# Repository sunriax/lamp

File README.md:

# Controllable Lamp (Signal) over Wireless LAN ([Shelly](https://shop.shelly.cloud/shelly-1-wifi-smart-home-automation#50))

## Project description

The PCB (lamp) can be controlled over a [Shelly](https://shop.shelly.cloud/shelly-1-wifi-smart-home-automation#50) wireless LAN module. It is attached to the PCB and can be controlled over the [Web Control](http://sunriax.github.io/lamp/) interface or any other software. Currently the lamp is designed for alerting. It changes the color within a given time. The lamp can be configured over the [Lamp Control](https://github.com/sunriax/lamp/releases/download/v1.0/Lamp.zip) application. Also the attached PC can be informed that an alert (over wireless LAN) occurrs. The current firmware can be downloaded [here](https://github.com/sunriax/lamp/releases/download/v1.0-Firmware/Firmware.zip). An ISP programmer for ATmega8 is necessary to flash the firmware onto the PCB.

## Project status

### Application

| Program     | Status |
|-------------|--------|
| [Web Control](http://sunriax.github.io/lamp/) |  |
| [Application](https://github.com/sunriax/lamp/releases/download/v1.0/Lamp.zip) |  |
|             |  |
| [Firmware](https://github.com/sunriax/lamp/releases/download/v1.0-Firmware/Firmware.zip)    |  |

### Schematic/PCB

| Board | Status |
|-------|:------:|
| [Schematic](https://cadlab.io/project/23814/main/circuit/cGNiL3BjYi5zY2g%3D) | ✔️ Done |
| [Board](https://cadlab.io/project/23814/main/circuit/cGNiL3BjYi5raWNhZF9wY2I%3D) | ✔️ Done |
| [Partlist](partlist.csv) | ✔️ Done |
| Production | ✔️ Done |
| [Assembly](pcb_assembled.png) | ✔️ Done |
| Case | ❌ Open |

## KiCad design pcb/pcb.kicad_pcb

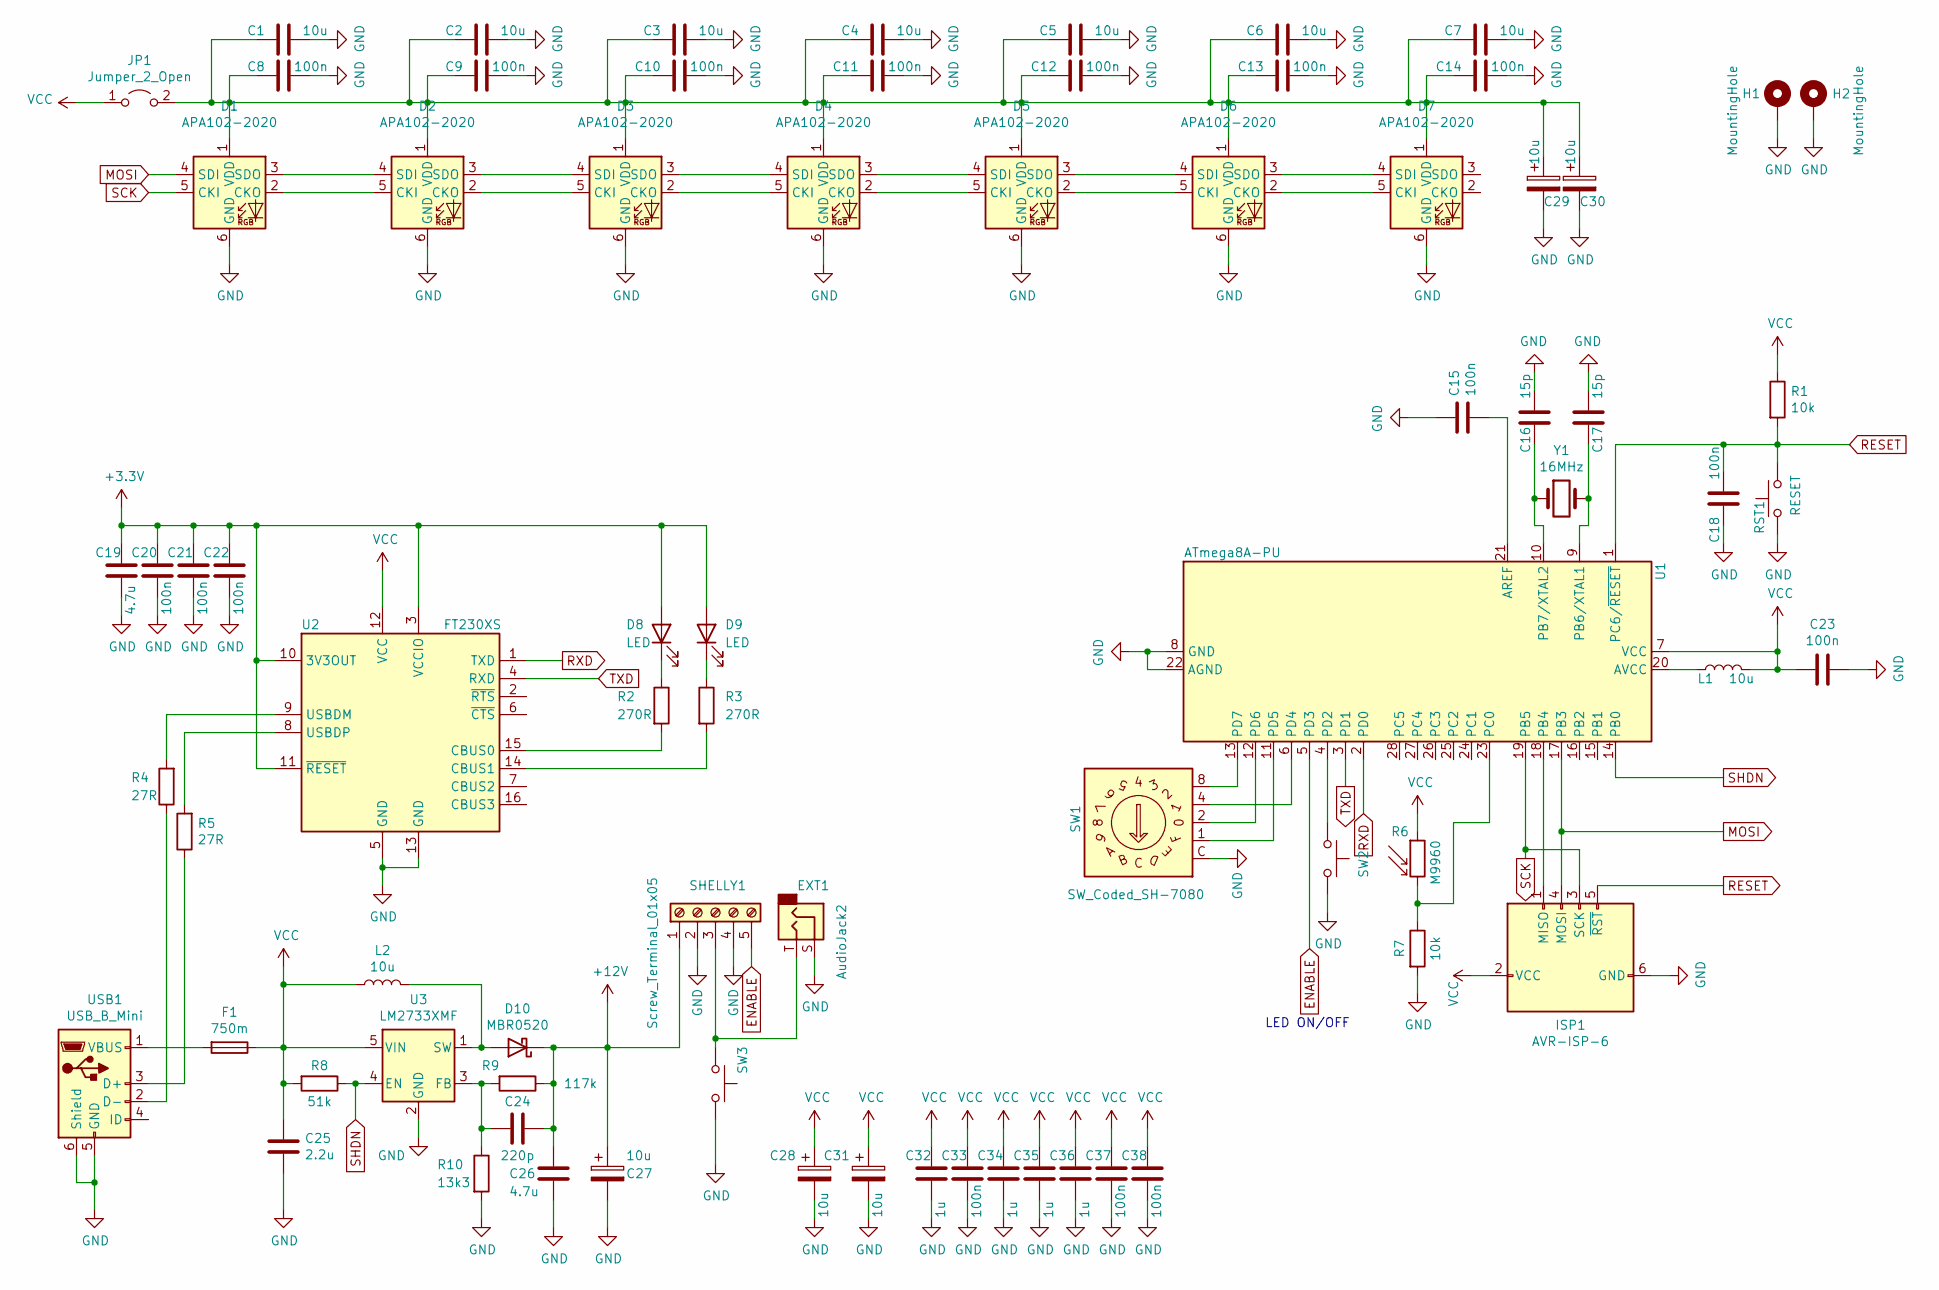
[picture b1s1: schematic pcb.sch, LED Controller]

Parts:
C1, C2, C3, C4, C5, C6, C7: 10u; C_0603_1608Metric
C8, C9, C10, C11, C12, C13, C14, C15, C18, C20, C21, C22, C23, C33, C37, C38: 100n; C_0603_1608Metric
C16, C17: 15p; C_0603_1608Metric
C19, C26: 4.7u; C_0603_1608Metric
C24: 220p; C_0603_1608Metric
C25: 2.2u; C_0603_1608Metric
C27, C28, C29, C30, C31: 10u; CP_Elec_4x5.8
C32, C34, C35, C36: 1u; C_0603_1608Metric
D1, D2, D3, D4, D5, D6, D7: APA102-2020; LED-APA102-2020
D8, D9: LED; LED_0603_1608Metric
D10: MBR0520; D_SOD-123
EXT1: AudioJack2; Jack_3.5mm_CUI_SJ-3523-SMT_Horizontal
F1: 750m; Fuse_Bourns_MF-SM_7.98x5.44mm
H1, H2: MountingHole; MountingHole_3.2mm_M3_Pad
ISP1: AVR-ISP-6; PinHeader_2x03_P2.54mm_Vertical_SMD
JP1: Jumper_2_Open; PinHeader_1x02_P2.54mm_Horizontal
L1: 10u; L_0805_2012Metric
L2: 10u; L_Bourns-SRN1060
R1, R7: 10k; R_0603_1608Metric
R2, R3: 270R; R_0603_1608Metric
R4, R5: 27R; R_0603_1608Metric
R6: M9960; R_LDR_5.2x5.2mm_P3.5mm_Horizontal
R8: 51k; R_0603_1608Metric
R9: 117k; R_0603_1608Metric
R10: 13k3; R_0603_1608Metric
RST1: RESET; SW_Push_1P1T-SH_NO_CK_KMR2xxG
SHELLY1: Screw_Terminal_01x05; TerminalBlock_Phoenix_MKDS-1,5-5_1x05_P5.00mm_Horizontal
SW1: SW_Coded_SH-7080; Nidec_Copal_SH-7040B
SW2, SW3: SW_Push_1P1T-SH_NO_CK_KMR2xxG
U1: ATmega8A-PU; DIP-28_W8.89mm_SMDSocket_LongPads
U2: FT230XS; SSOP-16_3.9x4.9mm_P0.635mm
U3: LM2733XMF; SOT-23-5
USB1: USB_B_Mini; USB_Mini-B_Lumberg_2486_01_Horizontal
Y1: 16MHz; Crystal_SMD_0603-2Pin_6.0x3.5mm

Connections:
+3V3: C19.2, C20.2, C21.2, C22.2, D8.2 (A), D9.2 (A), U2.3 (VCCIO), U2.10 (3V3OUT), U2.11 (~RESET)
+12V: C24.1, C26.1, C27.1, D10.1 (K), R9.1, SHELLY1.1
ENABLE: SHELLY1.5, U1.5 (PD3)
GND: C1.1, C2.1, C3.1, C4.1, C5.1, C6.1, C7.1, C8.1, C9.1, C10.1, C11.1, C12.1, C13.1, C14.1, C15.2, C16.2, C17.1, C18.2, C19.1, C20.1, C21.1, C22.1, C23.2, C25.2, C26.2, C27.2, C28.2, C29.2, C30.2, C31.2, C32.1, C33.1, C34.1, C35.1, C36.1, C37.1, C38.1, D1.6 (GND), D2.6 (GND), D3.6 (GND), D4.6 (GND), D5.6 (GND), D6.6 (GND), D7.6 (GND), EXT1.S, H1.1, H2.1, ISP1.6 (GND), R7.2, R10.2, RST1.1, SHELLY1.2, SHELLY1.4, SW1.C, SW2.1, SW3.1, U1.8 (GND), U1.22 (AGND), U2.5 (GND), U2.13 (GND), U3.2 (GND), USB1.5 (GND), USB1.6 (Shield)
MOSI: D1.4 (SDI), ISP1.4 (MOSI), U1.17 (PB3)
unnamed: C1.2, C2.2, C3.2, C4.2, C5.2, C6.2, C7.2, C8.2, C9.2, C10.2, C11.2, C12.2, C13.2, C14.2, C29.1, C30.1, D1.1 (VDD), D2.1 (VDD), D3.1 (VDD), D4.1 (VDD), D5.1 (VDD), D6.1 (VDD), D7.1 (VDD), JP1.2 (B)
unnamed: C15.1, U1.21 (AREF)
unnamed: C16.1, U1.10 (PB7/XTAL2), Y1.1
unnamed: C17.2, U1.9 (PB6/XTAL1), Y1.2
unnamed: C24.2, R9.2, R10.1, U3.3 (FB)
unnamed: D1.2 (CKO), D2.5 (CKI)
unnamed: D1.3 (SDO), D2.4 (SDI)
unnamed: D2.2 (CKO), D3.5 (CKI)
unnamed: D2.3 (SDO), D3.4 (SDI)
unnamed: D3.2 (CKO), D4.5 (CKI)
unnamed: D3.3 (SDO), D4.4 (SDI)
unnamed: D4.2 (CKO), D5.5 (CKI)
unnamed: D4.3 (SDO), D5.4 (SDI)
unnamed: D5.2 (CKO), D6.5 (CKI)
unnamed: D5.3 (SDO), D6.4 (SDI)
unnamed: D6.2 (CKO), D7.5 (CKI)
unnamed: D6.3 (SDO), D7.4 (SDI)
unnamed: D8.1 (K), R2.1
unnamed: D9.1 (K), R3.1
unnamed: D10.2 (A), L2.2, U3.1 (SW)
unnamed: EXT1.T, SHELLY1.3, SW3.2
unnamed: F1.2, USB1.1 (VBUS)
unnamed: ISP1.1 (MISO), U1.18 (PB4)
unnamed: L1.1, U1.20 (AVCC)
unnamed: R2.2, U2.15 (CBUS0)
unnamed: R3.2, U2.14 (CBUS1)
unnamed: R4.1, USB1.2 (D-)
unnamed: R4.2, U2.9 (USBDM)
unnamed: R5.1, USB1.3 (D+)
unnamed: R5.2, U2.8 (USBDP)
unnamed: R6.2, R7.1, U1.23 (PC0)
unnamed: SW1.1, U1.11 (PD5)
unnamed: SW1.2, U1.12 (PD6)
unnamed: SW1.4, U1.6 (PD4)
unnamed: SW1.8, U1.13 (PD7)
unnamed: SW2.2, U1.4 (PD2)
RESET: C18.1, ISP1.5 (~RST), R1.2, RST1.2, U1.1 (PC6/~RESET)
RXD: U1.2 (PD0), U2.1 (TXD)
SCK: D1.5 (CKI), ISP1.3 (SCK), U1.19 (PB5)
SHDN: R8.1, U1.14 (PB0), U3.4 (EN)
TXD: U1.3 (PD1), U2.4 (RXD)
VCC: C23.1, C25.1, C28.1, C31.1, C32.2, C33.2, C34.2, C35.2, C36.2, C37.2, C38.2, F1.1, ISP1.2 (VCC), JP1.1 (A), L1.2, L2.1, R1.1, R6.1, R8.2, U1.7 (VCC), U2.12 (VCC), U3.5 (VIN)

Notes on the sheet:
LED ON/OFF

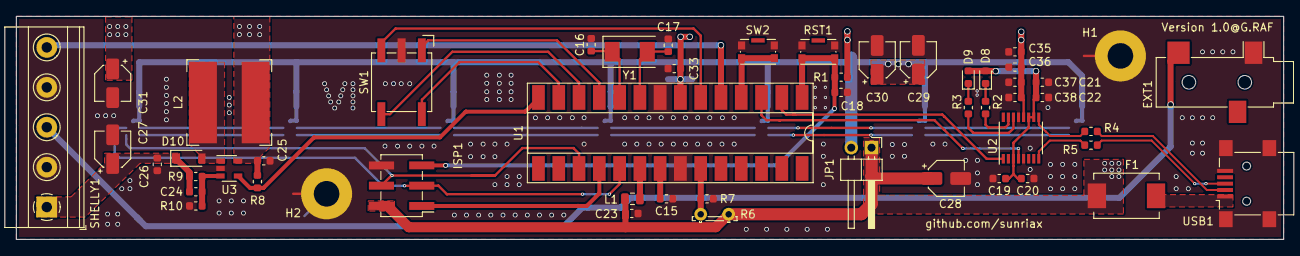
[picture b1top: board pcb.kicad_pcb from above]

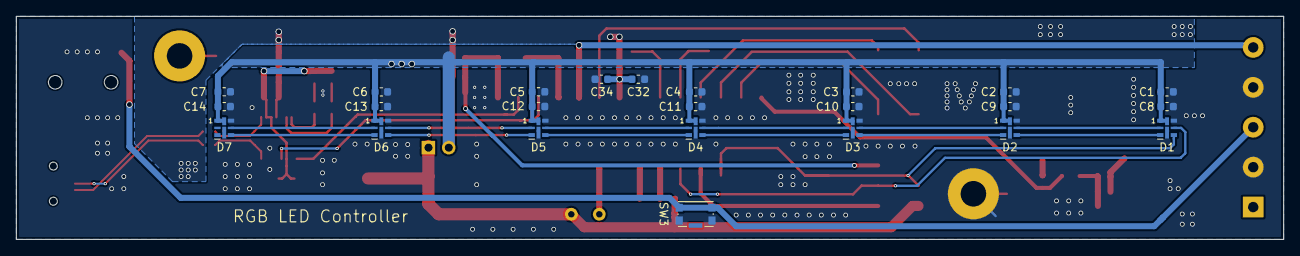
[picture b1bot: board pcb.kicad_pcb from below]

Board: 2 copper layers, 158.8 x 27.9 mm, 76 parts (24 on the bottom side), 47 nets.

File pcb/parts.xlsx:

|  |  |  |  |  |  |  | Platinen |  | Faktor
Item | Qty | Reference(s) | Value | Footprint | RS-Components | Price | Pieces | 1 | 25
1 | 7 | C1, C2, C3, C4, C5, C6, C7 | 10u | Capacitor_SMD:C_0603_1608Metric | 103-4121 | 0.182 | 100 | 18.2 | 36.4 | 2
2 | 16 | C8, C9, C10, C11, C12, C13, C14, C15, C18, C20, C21, C22, C23, C33, C37, C38 | 100n | Capacitor_SMD:C_0603_1608Metric | 133-5641 | 3.6999999999999998E-2 | 250 | 9.25 | 18.5 | 2
3 | 2 | C16, C17 | 15p | Capacitor_SMD:C_0603_1608Metric | 393-6659 | 2.9000000000000001E-2 | 25 | 0.72500000000000009 | 1.4500000000000002 | 2
4 | 2 | C19, C26 | 4.7u | Capacitor_SMD:C_0603_1608Metric | 815-1351 | 0.30399999999999999 | 25 | 7.6 | 15.2 | 2
5 | 1 | C24 | 220p | Capacitor_SMD:C_0603_1608Metric | 264-4539 | 3.6999999999999998E-2 | 25 | 0.92499999999999993 | 0.92499999999999993 | 1
6 | 1 | C25 | 2.2u | Capacitor_SMD:C_0603_1608Metric | 884-7289 | 0.26 | 50 | 13 | 13 | 1
7 | 5 | C27,C28, C29, C30, C31 | 10u | Capacitor_SMD:CP_Elec_4x5.8 | 568-919 | 0.372 | 5 | 1.8599999999999999 | 46.5 | 25
8 | 4 | C32, C34, C35, C36 | 1u | Capacitor_SMD:C_0603_1608Metric | 103-4110 | 8.5999999999999993E-2 | 100 | 8.6 | 8.6 | 1
9 | 7 | D1, D2, D3, D4, D5, D6, D7 | APA102-2020 | LED_SMD:LED-APA102-2020 | 180-8087 | 0.67600000000000005 | 0 | 0 | 0 | 1 | Wenn möglich nur 200 bestellen
 |  |  |  | https://www.mouser.at/ProductDetail/Adafruit/3341?qs=IP4CA2Y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 | 485-3341 (Mouser) | 6.05 | 1 | 6.05 | 108.89999999999999 | 18
 |  |  |  | https://de.aliexpress.com/item/32856952551.html |  | 32.26 | 0 | 0 | 0 | 1
10 | 2 | D8, D9 | LED | LED_SMD:LED_0603_1608Metric | 466-3728 | 0.128 | 40 | 5.12 | 10.24 | 2
11 | 1 | D10 | MBR0520 | Diode_SMD:D_SOD-123 | 739-0521 | 0.21199999999999999 | 10 | 2.12 | 6.36 | 3
12 | 1 | EXT1 | AudioJack2 | Connector_Audio:Jack_3.5mm_CUI_SJ-3523-SMT_Horizontal | 490-SJ-3523-SMT-TR (Mouser) | 0.75 | 1 | 0.75 | 18.75 | 25
 |  |  |  | https://de.aliexpress.com/item/1005001859629819.html |  | 12.09 | 0 | 0 | 0 | 3
13 | 1 | F1 | 750m | Fuse:Fuse_Bourns_MF-SM_7.98x5.44mm | 895-1647 | 0.46800000000000003 | 10 | 4.6800000000000006 | 14.040000000000003 | 3
14 | 2 | H1, H2 | MountingHole | MountingHole:MountingHole_3.2mm_M3_Pad | 528-738 | 8.3699999999999992 | 1 | 8.3699999999999992 | 8.3699999999999992 | 1
15 | 1 | ISP1 | AVR-ISP-6 | Connector_PinHeader_2.54mm:PinHeader_2x03_P2.54mm_Vertical_SMD | 765-6451 | 2.15 | 1 | 2.15 | 2.15 | 1
16 | 1 | JP1 | Jumper_2_Open | Connector_PinHeader_2.54mm:PinHeader_1x02_P2.54mm_Horizontal | 251-8430 | 0.78500000000000003 | 10 | 7.8500000000000005 | 23.55 | 3
17 | 1 | L1 | 10u | Inductor_SMD:L_0805_2012Metric | 124-1856 | 0.96 | 10 | 9.6 | 28.799999999999997 | 3
18 | 1 | L2 | L | Inductor_SMD:L_Bourns-SRN1060 | 772-9789 | 0.56799999999999995 | 5 | 2.84 | 14.2 | 5
19 | 2 | R1, R7 | 10k | Resistor_SMD:R_0603_1608Metric | 740-8892 | 1.6E-2 | 50 | 0.8 | 0.8 | 1
20 | 2 | R2, R3 | 270R | Resistor_SMD:R_0603_1608Metric | 679-0071 | 2.9000000000000001E-2 | 50 | 1.4500000000000002 | 1.4500000000000002 | 1
21 | 2 | R4, R5 | 27R | Resistor_SMD:R_0603_1608Metric | 679-0099 | 3.7999999999999999E-2 | 50 | 1.4500000000000002 | 1.4500000000000002 | 1
22 | 1 | R6 | M9960 | OptoDevice:R_LDR_5.2x5.2mm_P3.5mm_Horizontal | 914-6710 | 0.77400000000000002 | 10 | 7.74 | 23.22 | 3
23 | 1 | R8 | 51k | Resistor_SMD:R_0603_1608Metric | 679-0510 | 0.01 | 50 | 0.5 | 0.5 | 1
24 | 1 | R9 | 117k | Resistor_SMD:R_0603_1608Metric | 708-9047 | 0.39400000000000002 | 5 | 1.9700000000000002 | 9.8500000000000014 | 5
25 | 1 | R10 | 13k3 | Resistor_SMD:R_0603_1608Metric | 678-9756 | 3.7999999999999999E-2 | 50 | 1.9 | 1.9 | 1
26 | 1 | RST1,SW2,SW3 | RESET | Button_Switch_SMD:SW_Push_1P1T-SH_NO_CK_KMR2xxG | 793-1601 | 0.38 | 1 | 0.38 | 9.5 | 25
27 | 1 | SHELLY1 | Screw_Terminal_01x05 | TerminalBlock_Phoenix:TerminalBlock_Phoenix_MKDS-1,5-5_1x05_P5.00mm_Horizontal | 858-8435 | 0.57599999999999996 | 100 | 57.599999999999994 | 57.599999999999994 | 1
28 | 1 | SW1 | SW_Coded_SH-7080 | Button_Switch_SMD:Nidec_Copal_SH-7040B | 179-6934 | 3.9950000000000001 | 2 | 7.99 | 103.87 | 13
29 | 1 | U1 | ATmega8A-PU | Package_DIP:DIP-28_W8.89mm_SMDSocket_LongPads | 131-0372 | 1.885 | 2 | 3.77 | 49.01 | 13
30 | 1 | DIL-Sockel SMD Montage |  | DIP-28-SMD | 702-0553 | 2.226 | 1 | 2.226 | 55.65 | 25
31 | 1 | U2 | FT230XS | Package_SO:SSOP-16_3.9x4.9mm_P0.635mm | 757-0010 | 1.7649999999999999 | 2 | 3.53 | 45.89 | 13
32 | 1 | U3 | LM2733XMF | Package_TO_SOT_SMD:SOT-23-5 | 533-5424 | 2.09 | 1 | 2.09 | 52.25 | 25
33 | 1 | USB1 | USB_B_Mini | Connector_USB:USB_Mini-B_Lumberg_2486_01_Horizontal | 186-4902 | 1.1639999999999999 | 5 | 5.8199999999999994 | 29.099999999999998 | 5
34 | 1 | Y1 | 16MHz | Crystal:Crystal_SMD_0603-2Pin_6.0x3.5mm | 171-0633 | 0.60099999999999998 | 10 | 6.01 | 18.03 | 3
35 | 1 | Platine |  |  | multi-cb | 140.55000000000001 | 1 | 152.05000000000001 | 152.05000000000001 | 1
36 | 1 | USB Kabel A/mini B |  |  | 186-2818 | 3.39 | 0 | 0 | 0 | 25
 |  |  |  |  | B00I97P5NI (Amazon) | 0.98 | 1 | 0.98 | 24.5 | 25
37 | 1 | USB Netzteil |  |  | 123-6686 | 7.19 | 0 | 0 | 0 | 25
 |  |  |  |  | B08P3M9JW8 (Amazon) | 12.59 | 1 | 12.59 | 100.72 | 8
38 | 1 | Shelly1 |  |  | B07NS8M4Y1 (Amazon) | 23.95 | 2 | 47.9 | 622.69999999999993 | 13
 |  |  |  |  |  |  | Summe | 428.43599999999998 | 1735.9749999999999
 |  |  |  |  |  |  |  | Stückpreis | 69.438999999999993
 |  |  |  |  |  |  |  | Gehäuse | 30
 |  |  |  |  |  |  |  | Gesamt | 99.438999999999993

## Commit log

2021-07-28 Fix typo
2021-07-28 Extend releases
2021-07-29 Add description
2021-07-29 Create CNAME
2021-07-29 Update CNAME

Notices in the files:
README.md:
License: GPL v3
